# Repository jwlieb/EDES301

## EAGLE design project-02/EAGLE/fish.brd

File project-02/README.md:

#EDES301 Project 2: Talking Fish PCB

This project is a compact printed circuit board for the talking fish assistant implementation explored in Project 1.

The EAGLE folder contains the library, schematic, and layout for the PCB. 

The MFG folder contains the manufacturing information including a BOM, gerber files, and additional screenshots for assembly.

More information can be found in the docs folder, which houses the system block diagram, mechanical drawing, schematics pdf, and addional images of the top and bottom layers of the board.

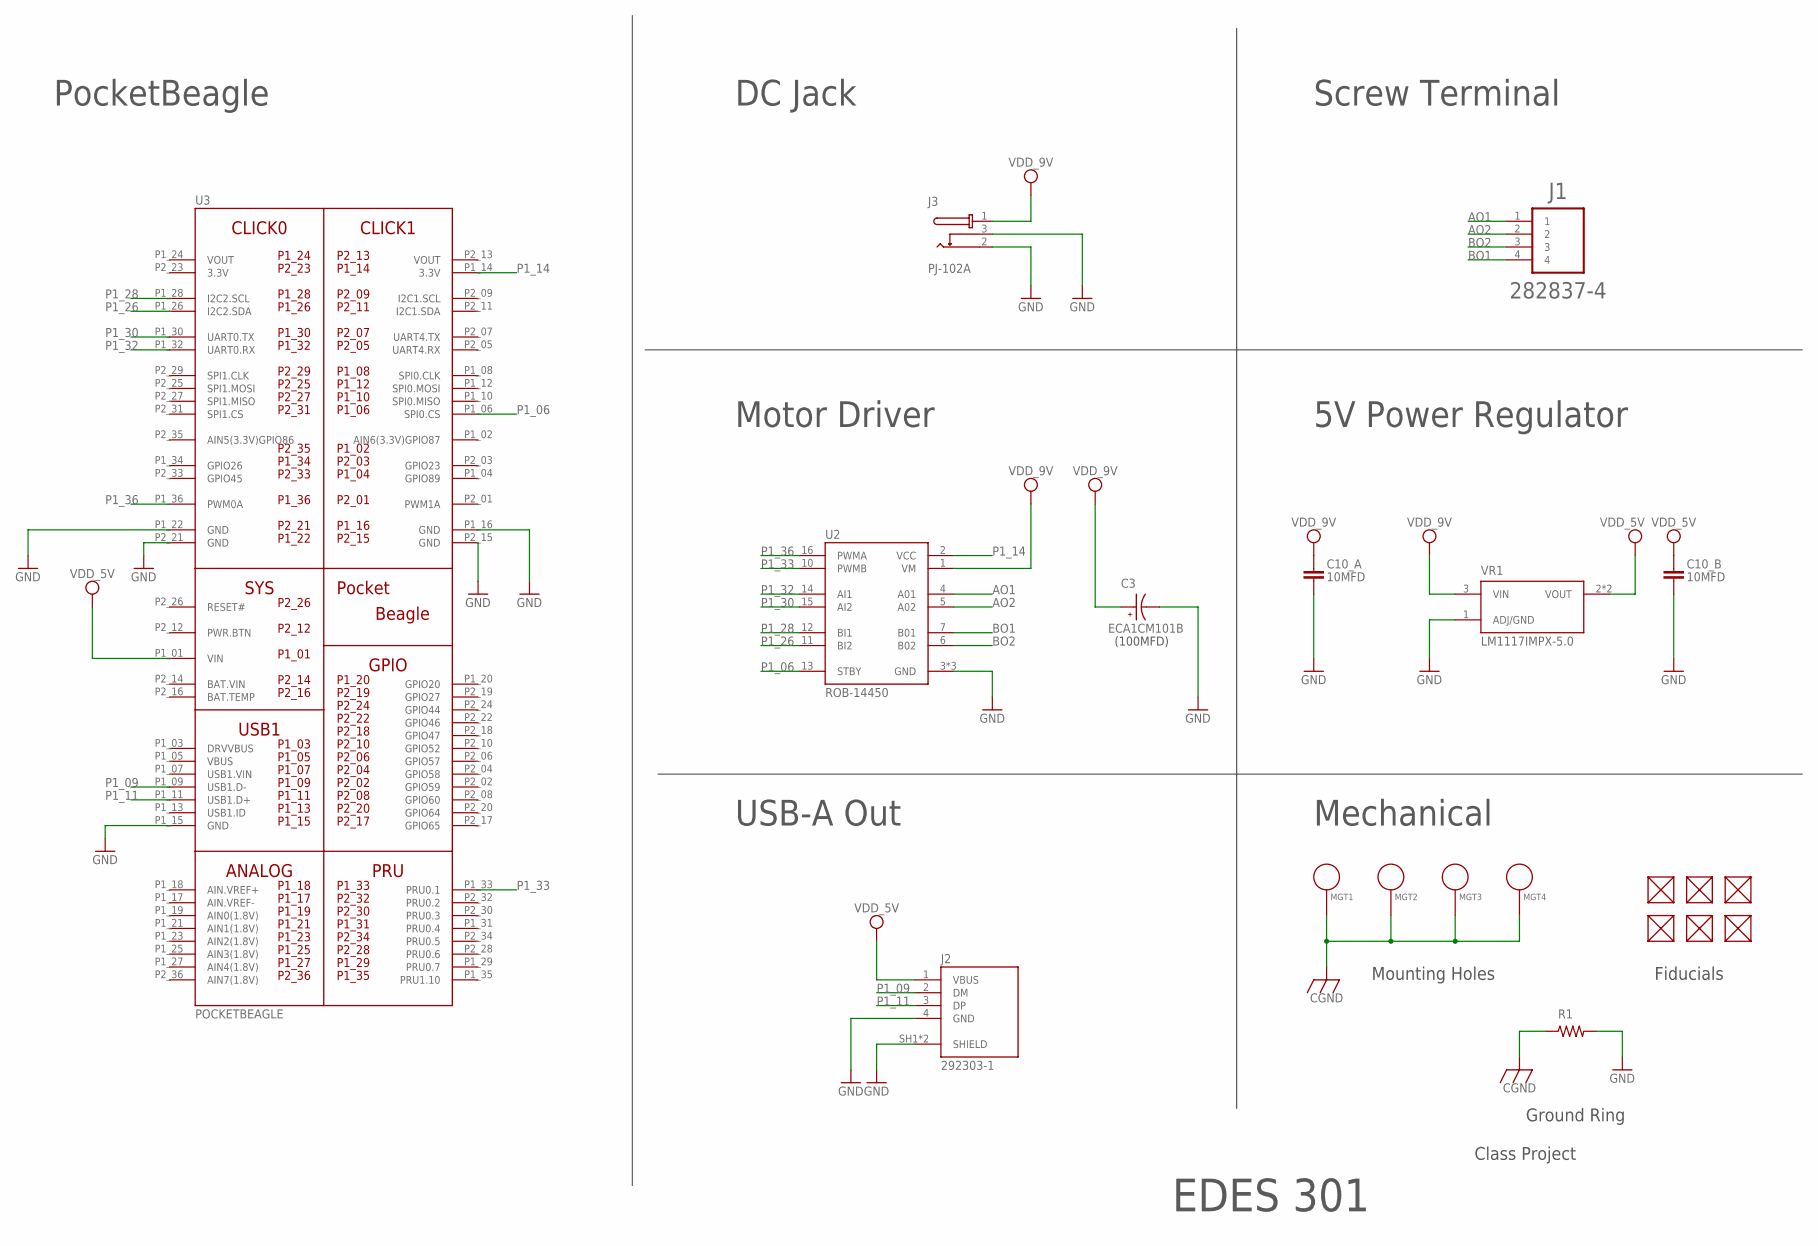
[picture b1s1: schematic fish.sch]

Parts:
C3: ECA1CM101B; CAPPRD500W50D500H1100
C10_A, C10_B: 10MFD; C0805
FUD1, FUD2, FUD3, FUD4, FUD5, FUD6: FIDUCIAL; FIDUCIAL_40MIL
J1: 282837-4; TE_282837-4
J2: 292303-1; TE_292303-1
J3: PJ-102A; CUI_PJ-102A
MGT1, MGT2, MGT3, MGT4: MOUNTING_HOLE
R1: 1 Ohm; R0402
U2: ROB-14450; MODULE_ROB-14450
U3: POCKETBEAGLE
VR1: LM1117IMPX-5.0; SOT230P700X180-4N

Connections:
3.3V: U3.P2_23 (3.3V)
AO1: J1.1, U2.4 (A01)
AO2: J1.2, U2.5 (A02)
BAT.VIN: U3.P2_14 (BAT.VIN)
BO1: J1.4, U2.7 (B01)
BO2: J1.3, U2.6 (B02)
CGND: MGT1.P$1, MGT2.P$1, MGT3.P$1, MGT4.P$1, R1.1
GND: C3.N, C10_A.2, C10_B.2, J2.4 (GND), J2.SH1 (SHIELD), J2.SH2 (SHIELD), J3.2, J3.3, R1.2, U2.3 (GND), U2.8 (GND), U2.9 (GND), U3.P1_15 (GND), U3.P1_16 (GND), U3.P1_22 (GND), U3.P2_15 (GND), U3.P2_21 (GND), VR1.1 (ADJ/GND)
P1_06: U2.13 (STBY), U3.P1_06 (SPI0.CS)
P1_09: J2.2 (DM), U3.P1_09 (USB1.D-)
P1_11: J2.3 (DP), U3.P1_11 (USB1.D+)
P1_14: U2.2 (VCC), U3.P1_14 (3.3V)
P1_26: U2.11 (BI2), U3.P1_26 (I2C2.SDA)
P1_28: U2.12 (BI1), U3.P1_28 (I2C2.SCL)
P1_30: U2.15 (AI2), U3.P1_30 (UART0.TX)
P1_32: U2.14 (AI1), U3.P1_32 (UART0.RX)
P1_33: U2.10 (PWMB), U3.P1_33 (PRU0.1)
P1_36: U2.16 (PWMA), U3.P1_36 (PWM0A)
VDD_5V: C10_B.1, J2.1 (VBUS), U3.P1_01 (VIN), VR1.2 (VOUT), VR1.4 (VOUT)
VDD_9V: C3.P, C10_A.1, J3.1, U2.1 (VM), VR1.3 (VIN)
VOUT: U3.P1_24 (VOUT), U3.P2_13 (VOUT)

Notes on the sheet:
EDES 301
Class Project
PocketBeagle
DC Jack
Screw Terminal
5V Power Regulator
Motor Driver
USB-A Out
Mechanical
(100MFD)
Fiducials
Mounting Holes
Ground Ring

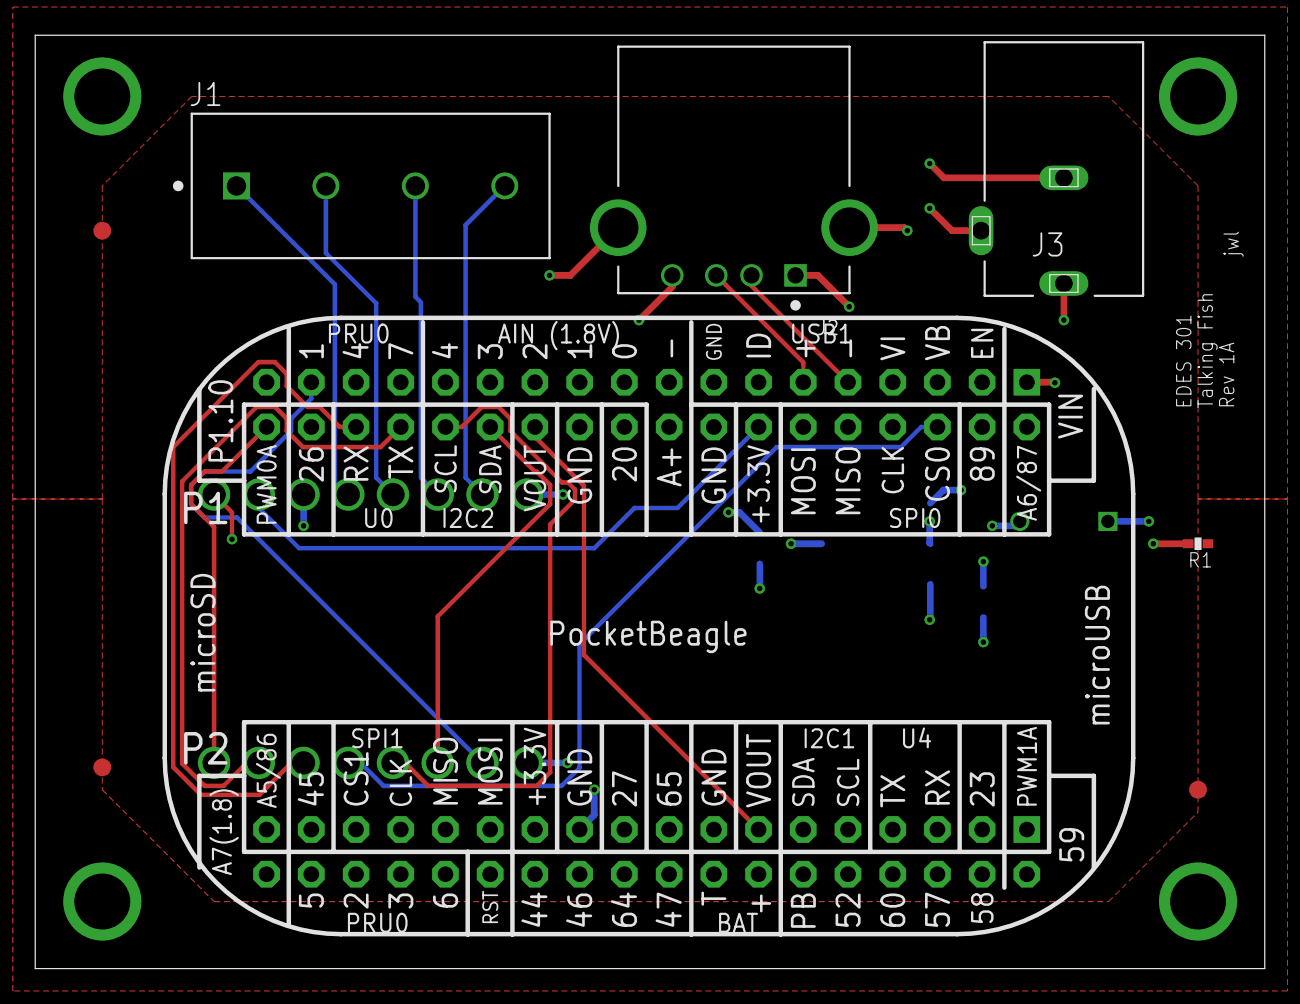
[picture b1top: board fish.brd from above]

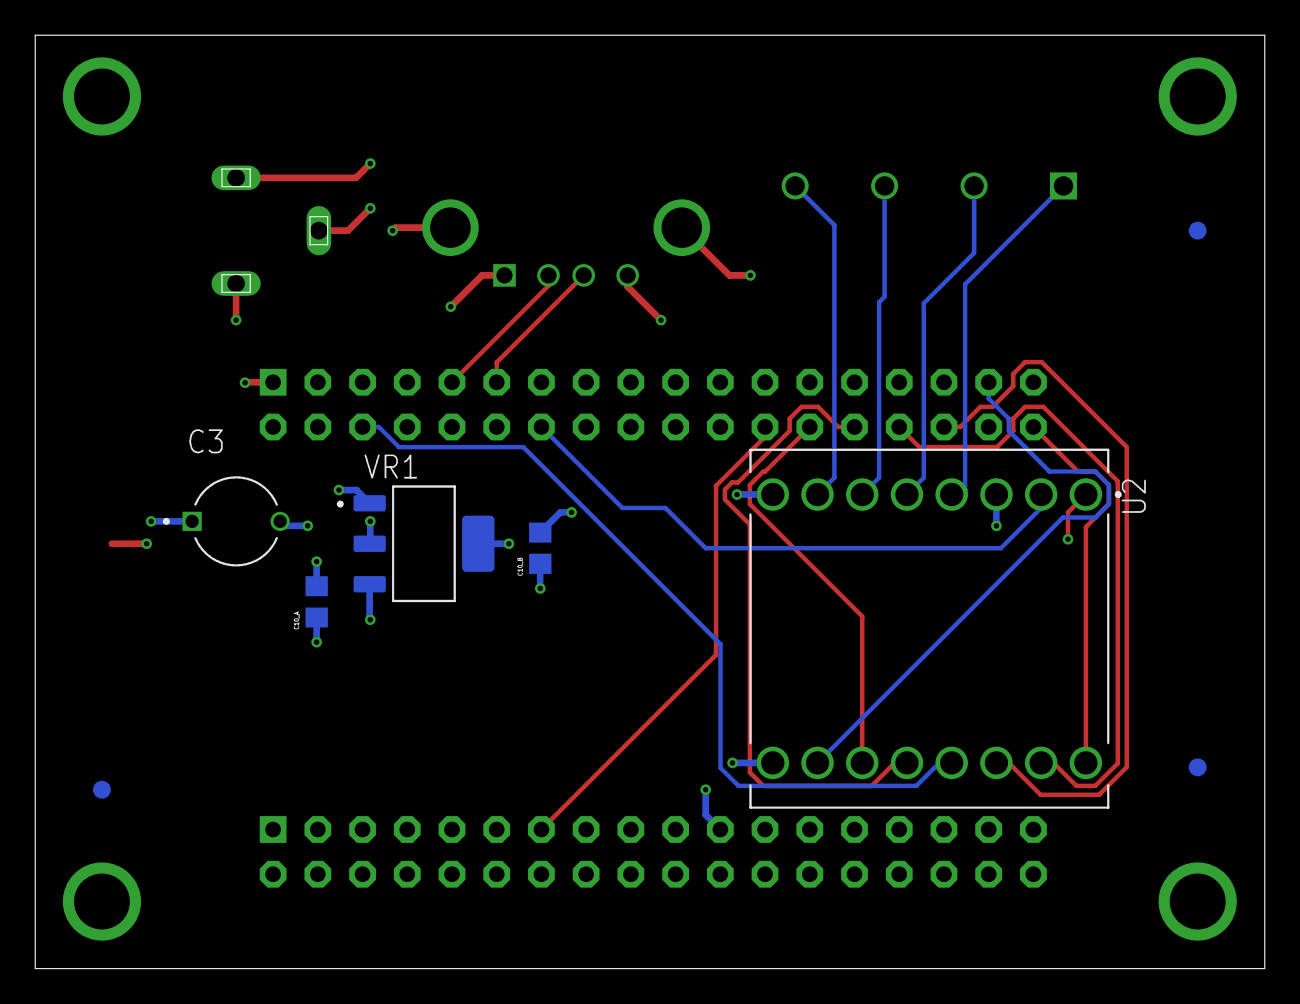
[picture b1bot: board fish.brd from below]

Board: 4 copper layers, 69.8 x 53.0 mm, 20 parts (9 on the bottom side), 19 nets.

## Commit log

2025-09-23 Updating README.md
2025-10-06 project 1 folder + proposal
2025-10-06 updated proposal
2025-10-08 class simple calc
2025-10-08 extend simple_calc to handle other operators + python2 support
2025-10-08 blink led
2025-10-08 implemented button.py
2025-10-08 fix button.py
2025-10-08 fix one more issue in button.py...
2025-10-10 update project 1 proposal
2025-10-25 design
2025-12-03 move from jwlieb/fish-assistant
2025-12-03 actually move from fish-assistant
2025-12-03 now?
2025-12-03 one step back for two steps forward?
2025-12-03 two steps forward
2025-12-03 move docs back...
2025-12-13 update from fish-assistant repo + proper file headers
2025-12-18 bulk project 2 upload
2025-12-18 project 2 readme (forgot to gitignore dsstore earlier oops)
